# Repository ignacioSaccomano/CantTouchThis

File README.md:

# CantTouchThis
Porque un problema persistente requiere una solución estridente.

## ¿En qué consiste?
Este repositorio contiene los archivos necesarios para poder crear un circuito cuyo propósito es prevenir que el usuario se toque la cara y así prevenir la contracción de enfermedades infecciosas.

## ¿Cómo funciona?
Simple. Hay un circuito que debe hacerse dos veces, ya que se usa a modo de pulsera. Luego está el circuito del receptor (especificado en el archivo) que va a modo de collar o pin expuesto. Cuando el receptor detecta que una pulsera se aproxima hace sonar un zumbador para alertar inmediatamente al usuario.

## Aclaración importante
Este proyecto fue hecho para la [feria de ciencias de la universidad de Favaloro](https://www.favaloro.edu.ar/feria-de-ciencias-2020-2/). Todos los archivos tienen que ejecutarse con el software gratuito [Kicad](https://kicad.org/).

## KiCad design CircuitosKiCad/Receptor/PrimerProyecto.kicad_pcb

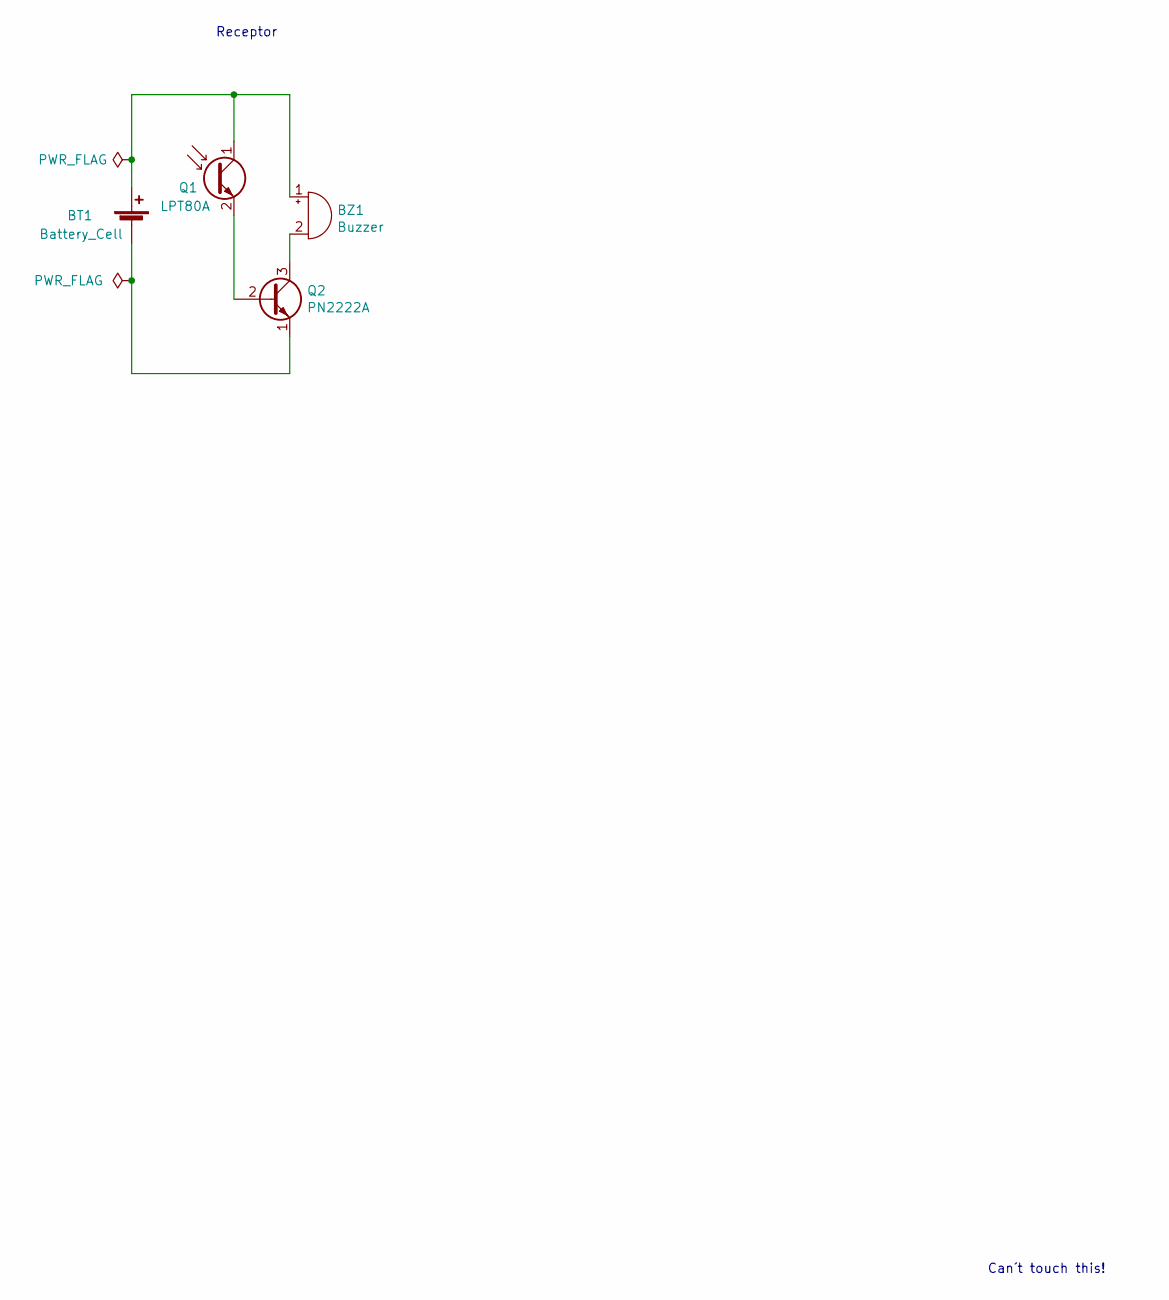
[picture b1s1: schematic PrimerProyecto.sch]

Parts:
BT1: Battery_Cell; BatteryHolder_Keystone_1058_1x2032
BZ1: Buzzer; Buzzer_15x7.5RM7.6
Q1: LPT80A; Osram_LPT80A
Q2: PN2222A; TO-92_Inline

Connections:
unnamed: BT1.1 (+), BZ1.1 (-), Q1.1 (C)
unnamed: BT1.2 (-), Q2.1 (E)
unnamed: BZ1.2 (+), Q2.3 (C)
unnamed: Q1.2 (E), Q2.2 (B)

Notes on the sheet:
Can´t touch this!
Receptor

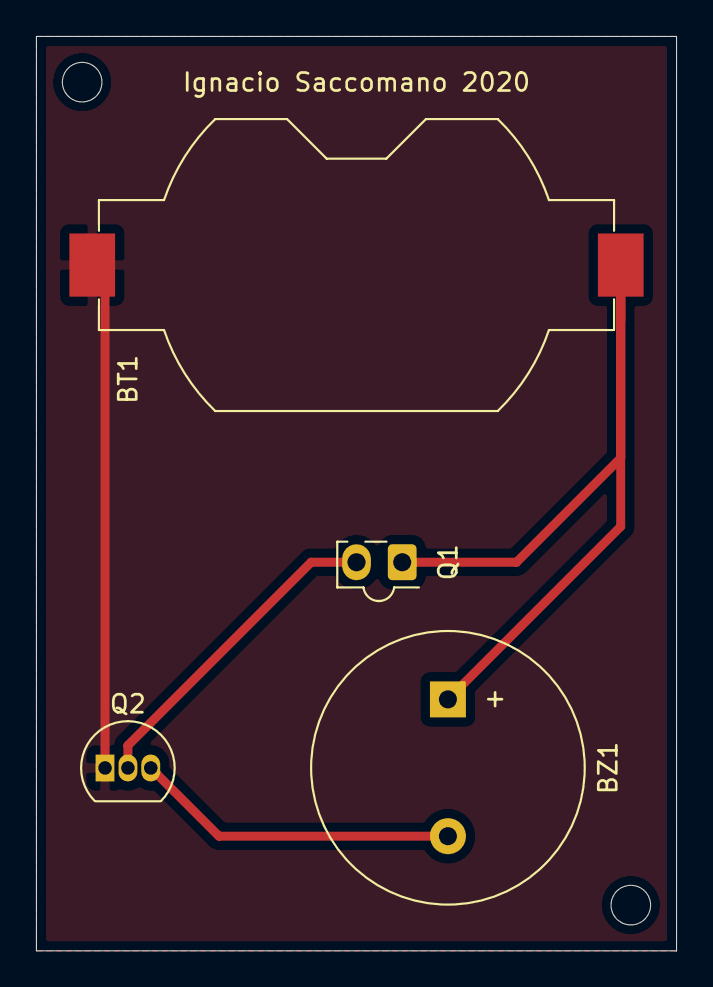
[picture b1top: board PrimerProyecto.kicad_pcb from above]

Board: 2 copper layers, 35.6 x 50.8 mm, 4 parts (0 on the bottom side), 4 nets.

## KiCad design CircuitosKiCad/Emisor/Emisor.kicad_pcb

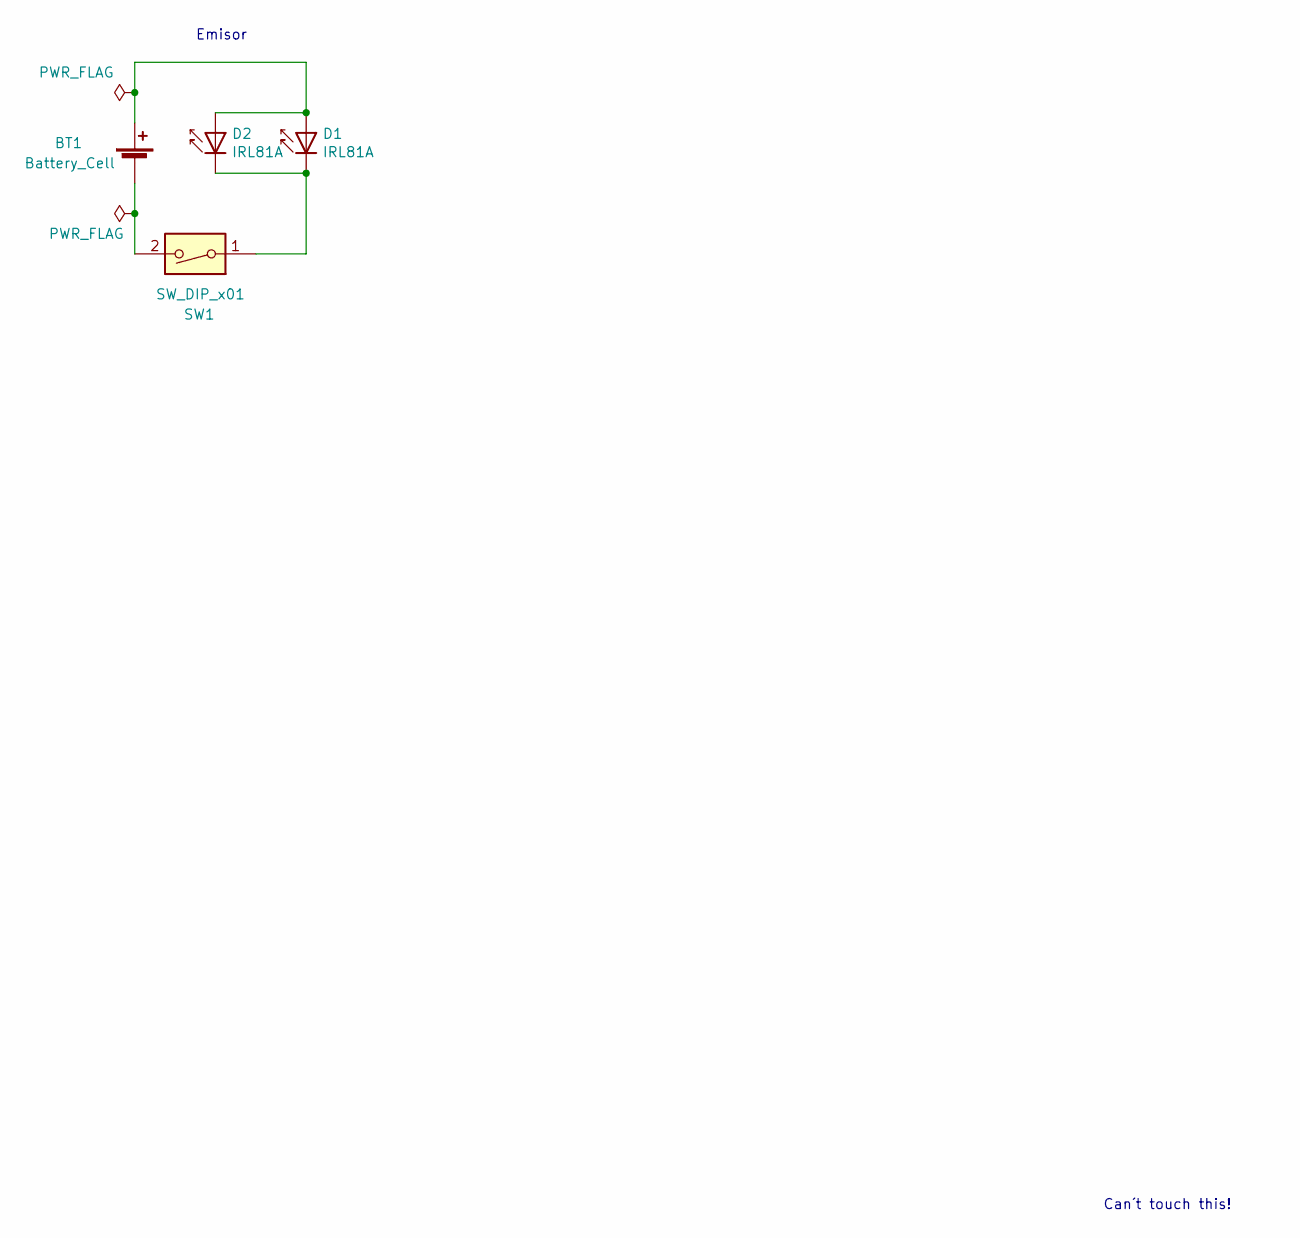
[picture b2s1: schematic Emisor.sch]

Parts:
BT1: Battery_Cell; BatteryHolder_Keystone_1058_1x2032
D1, D2: IRL81A; LED_SideEmitter_Rectangular_W4.5mm_H1.6mm
SW1: SW_DIP_x01; SW_DIP_SPSTx01_Slide_6.7x4.1mm_W7.62mm_P2.54mm_LowProfile

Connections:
unnamed: BT1.1 (+), D1.2 (A), D2.2 (A)
unnamed: BT1.2 (-), SW1.2
unnamed: D1.1 (K), D2.1 (K), SW1.1

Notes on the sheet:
Can´t touch this!
Emisor

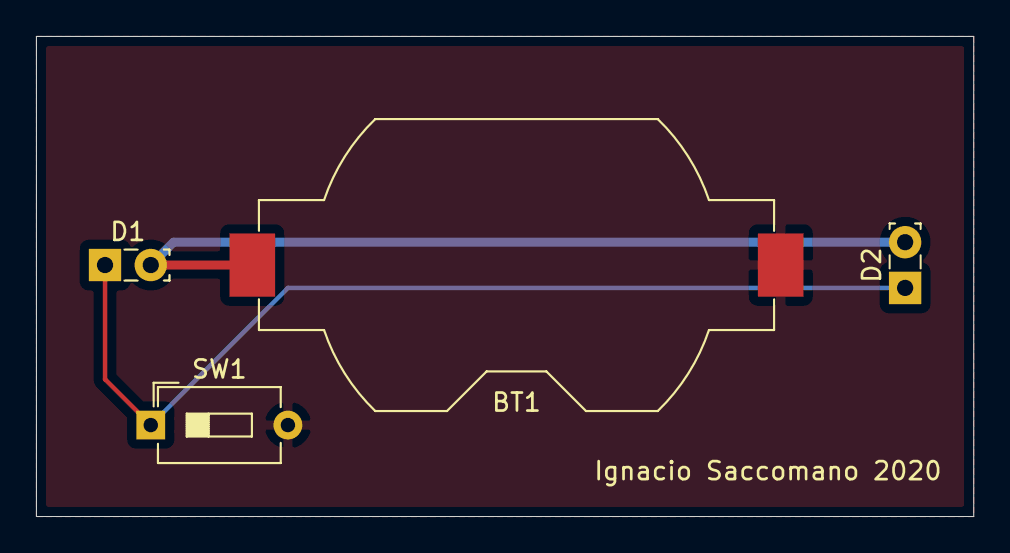
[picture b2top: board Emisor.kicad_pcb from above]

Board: 2 copper layers, 52.1 x 26.7 mm, 4 parts (0 on the bottom side), 3 nets.

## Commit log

2020-11-29 Update README.md
    Agrego descripción básica del proyecto.
2020-12-04 Agrego los archivos de los circuitos correspondientes al emisor (pulsera) y receptor (collar o broche).
2020-12-04 Aclaración.
2020-12-07 Agrego archivos gerber para fabricar las placas
